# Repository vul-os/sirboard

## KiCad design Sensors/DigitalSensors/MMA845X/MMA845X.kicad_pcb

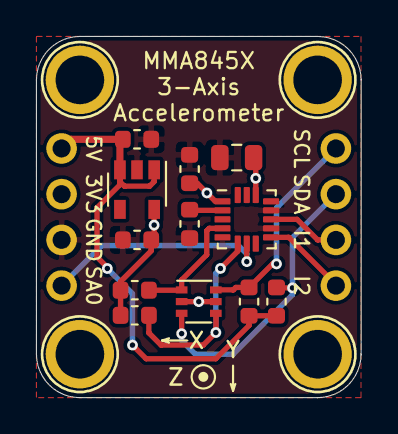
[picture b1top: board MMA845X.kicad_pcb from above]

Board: 2 copper layers, 18.0 x 20.1 mm, 18 parts (0 on the bottom side), 11 nets.

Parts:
C1, C3: 1uF; C_0603_1608Metric
C2, C4: 100nF; C_0603_1608Metric
C5: 4.7uF; C_0805_2012Metric
H1, H2, H3, H4: MountingHole; MountingHole_M2.5_SirBoard
J1, J2: Conn_01x04; PinHeader_1x04_P2.54mm_Vertical
Q1: BSS138DW; SOT-363_SC-70-6
R1, R2, R3, R4: 4K7; R_0603_1608Metric
U1: AP2127K-3.3; SOT-23-5
U2: MMA8451; QFN-COL-16-P=0.5

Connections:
3V3: C2.1, C3.1, C5.1, J1.2, Q1.2, Q1.5, R1.2, R3.2, U1.5, U2.1, U2.14
5V: C1.1, J1.1, R2.1, R4.1, U1.1, U1.3
GND: C1.2, C2.2, C3.2, C4.2, C5.2, J1.3, U1.2, U2.5, U2.10, U2.12
INT1: J2.3, U2.11
INT2: J2.4, U2.9
unnamed: C4.1, U2.2
SA0: J1.4, U2.7
SCL_3V3: Q1.1, R1.1, U2.4
SCL_5V: J2.1, Q1.6, R2.2
SDA_3V3: Q1.4, R3.1, U2.6
SDA_5V: J2.2, Q1.3, R4.2

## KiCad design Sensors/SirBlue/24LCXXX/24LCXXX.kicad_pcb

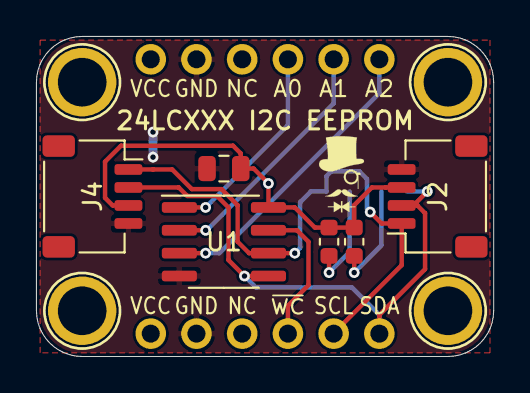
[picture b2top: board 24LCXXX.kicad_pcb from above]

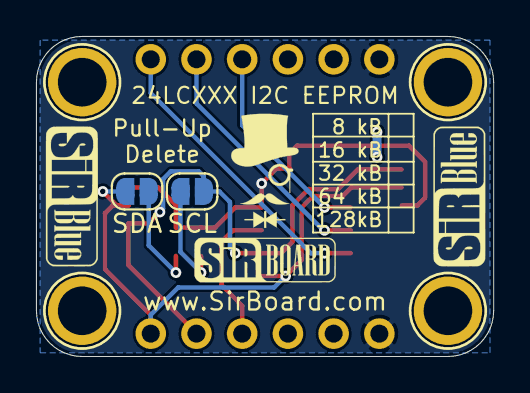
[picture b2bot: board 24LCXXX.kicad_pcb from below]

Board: 2 copper layers, 25.4 x 17.8 mm, 14 parts (4 on the bottom side), 10 nets.

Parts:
C1: 10uF; C_0805_2012Metric
H1, H2, H3, H4: MountingHole; MountingHole_M2.5_SirBoard
J1, J3: Conn_01x06; PinHeader_1x06_P2.54mm_Vertical
J2, J4: Conn_01x04; JST_SH_SM04B-SRSS-TB_1x04-1MP_P1.00mm_Horizontal
R1, R2: 10K; R_0603_1608Metric
SCL: SolderJumper_2_Open; SolderJumper-2_P1.3mm_Open_RoundedPad1.0x1.5mm
SDA: SolderJumper_2_Open; SolderJumper-2_P1.3mm_Open_RoundedPad1.0x1.5mm
U1: 24LC512; SOIC-8_3.9x4.9mm_P1.27mm

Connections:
#WC: J1.4, U1.7
A0: J3.4, U1.1
A1: J3.5, U1.2
A2: J3.6, U1.3
GND: C1.2, J1.2, J2.4, J3.2, J4.4, U1.4
unnamed: R1.2, SDA.2
unnamed: R2.2, SCL.2
SCL: J1.5, J2.1, J4.1, SCL.1, U1.6
SDA: J1.6, J2.2, J4.2, SDA.1, U1.5
VCC: C1.1, J1.1, J2.3, J3.1, J4.3, R1.1, R2.1, U1.8

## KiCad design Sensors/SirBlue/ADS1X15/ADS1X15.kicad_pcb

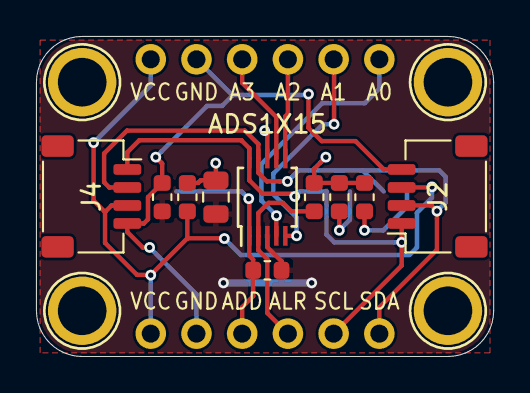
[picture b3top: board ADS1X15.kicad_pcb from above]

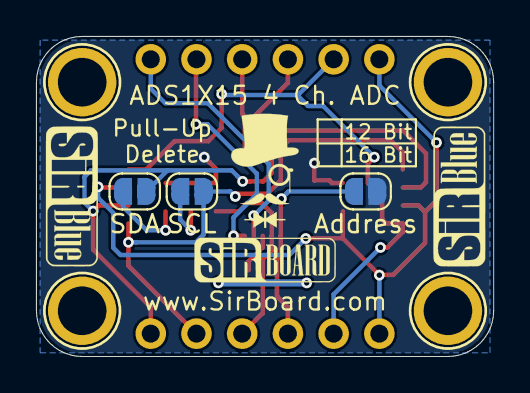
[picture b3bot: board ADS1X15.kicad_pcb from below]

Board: 2 copper layers, 25.4 x 17.8 mm, 19 parts (5 on the bottom side), 14 nets.

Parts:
ADS1X15: ADS1X15; TSSOP-10_3x3mm_P0.5mm
Address: SolderJumper_2_Open; SolderJumper-2_P1.3mm_Open_RoundedPad1.0x1.5mm
C1: 10uF; C_0805_2012Metric
FB1, FB2: Ferrite_Bead; L_0603_1608Metric
H1, H2, H3, H4: MountingHole; MountingHole_M2.5_SirBoard
J1, J3: Conn_01x06; PinHeader_1x06_P2.54mm_Vertical
J2, J4: Conn_01x04; JST_SH_SM04B-SRSS-TB_1x04-1MP_P1.00mm_Horizontal
R1, R2, R3, R4: 10K; R_0603_1608Metric
SCL: SolderJumper_2_Open; SolderJumper-2_P1.3mm_Open_RoundedPad1.0x1.5mm
SDA: SolderJumper_2_Open; SolderJumper-2_P1.3mm_Open_RoundedPad1.0x1.5mm

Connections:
ADDRESS: ADS1X15.1, Address.2, J1.3, R4.1
ALERT: ADS1X15.2, J1.4, R3.2
Ain0: ADS1X15.4, J3.6
Ain1: ADS1X15.5, J3.5
Ain2: ADS1X15.6, J3.4
Ain3: ADS1X15.7, J3.3
GND: FB2.1, J1.2, J2.4, J3.2, J4.4
GND_B: ADS1X15.3, C1.2, FB2.2, R4.2
unnamed: R1.2, SCL.2
unnamed: R2.2, SDA.2
SCL: ADS1X15.10, J1.5, J2.1, J4.1, SCL.1
SDA: ADS1X15.9, J1.6, J2.2, J4.2, SDA.1
VCC: FB1.1, J1.1, J2.3, J3.1, J4.3
VCC_B: ADS1X15.8, Address.1, C1.1, FB1.2, R1.1, R2.1, R3.1

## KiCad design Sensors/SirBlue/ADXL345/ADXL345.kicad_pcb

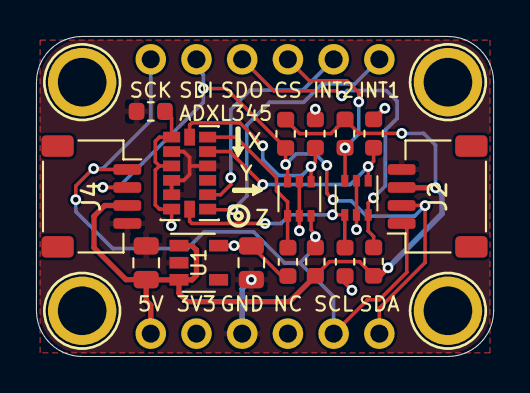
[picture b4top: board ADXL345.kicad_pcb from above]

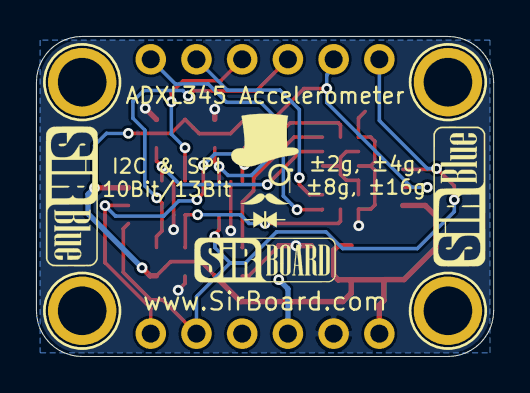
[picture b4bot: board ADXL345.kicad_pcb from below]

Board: 2 copper layers, 25.4 x 17.8 mm, 23 parts (2 on the bottom side), 13 nets.

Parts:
ADXL345: ADXL345; LGA-14_3x5mm_P0.8mm_LayoutBorder1x6y
C1, C4: 10uF; C_0805_2012Metric
C2: 100nF; C_0603_1608Metric
H1, H2, H3, H4: MountingHole; MountingHole_M2.5_SirBoard
J1, J3: Conn_01x06; PinHeader_1x06_P2.54mm_Vertical
J2, J4: Conn_01x04; JST_SH_SM04B-SRSS-TB_1x04-1MP_P1.00mm_Horizontal
Q1, Q2: BSS138DW; SOT-363_SC-70-6
R1, R2, R3, R4, R5, R6, R7, R8: 10K; R_0603_1608Metric
U1: AP2127K-3.3; SOT-23-5

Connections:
3V3: ADXL345.1, ADXL345.3, ADXL345.6, C2.1, C4.1, J1.2, Q1.2, Q1.5, Q2.2, Q2.5, R1.2, R3.2, R5.2, R7.2, U1.5
5V: C1.1, J1.1, J2.3, J4.3, R2.1, R4.1, R6.1, R8.1, U1.1, U1.3
CS_3V3: ADXL345.7, Q1.4, R3.1
CS_5V: J3.4, Q1.3, R4.2
GND: ADXL345.2, ADXL345.4, ADXL345.5, ADXL345.11, C1.2, C2.2, C4.2, J1.3, J2.4, J4.4, U1.2
INT1: ADXL345.8, J3.6
INT2: ADXL345.9, J3.5
SCL_3V3: ADXL345.14, Q2.1, R5.1
SCL_5V: J1.5, J2.1, J3.1, J4.1, Q2.6, R6.2
SDA_3V3: ADXL345.13, Q2.4, R7.1
SDA_5V: J1.6, J2.2, J3.2, J4.2, Q2.3, R8.2
SDO_3V3: ADXL345.12, Q1.1, R1.1
SDO_5V: J3.3, Q1.6, R2.2

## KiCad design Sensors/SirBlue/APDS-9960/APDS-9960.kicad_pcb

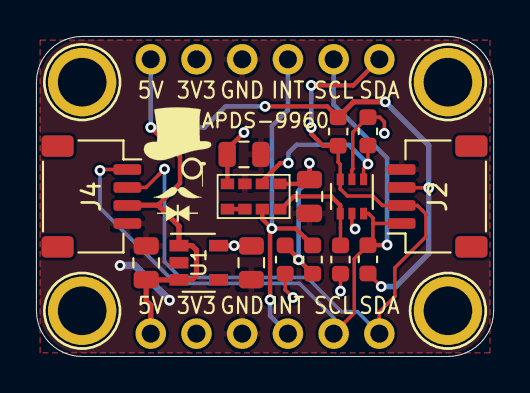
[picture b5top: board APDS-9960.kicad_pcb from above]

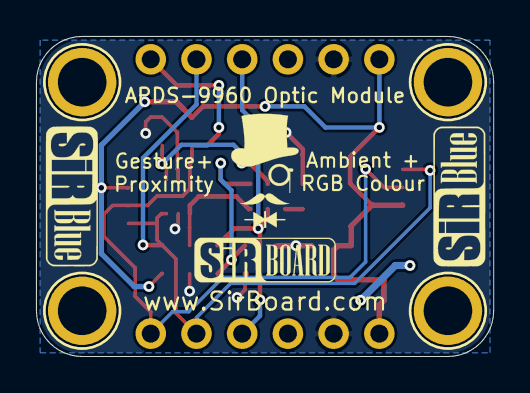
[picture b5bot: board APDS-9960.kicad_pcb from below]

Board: 2 copper layers, 25.4 x 17.8 mm, 21 parts (2 on the bottom side), 10 nets.

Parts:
C1, C4: 10uF; C_0805_2012Metric
C2, C3: 1uF; C_0805_2012Metric
H1, H2, H3, H4: MountingHole; MountingHole_M2.5_SirBoard
J1, J3: Conn_01x06; PinHeader_1x06_P2.54mm_Vertical
J2, J4: Conn_01x04; JST_SH_SM04B-SRSS-TB_1x04-1MP_P1.00mm_Horizontal
Q2: BSS138DW; SOT-363_SC-70-6
R1: 22E; R_0603_1608Metric
R2, R5, R6, R7, R8: 10K; R_0603_1608Metric
U1: AP2127K-3.3; SOT-23-5
U2: APDS-9960; DFN8_2.4mmX4mm_P=0.72

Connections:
3V3: C2.1, C4.1, J1.2, J3.2, Q2.2, Q2.5, R1.1, R5.2, R7.2, U1.5, U2.5
5V: C1.1, J1.1, J2.3, J3.1, J4.3, R6.1, R8.1, U1.1, U1.3
GND: C1.2, C2.2, C3.2, C4.2, J1.3, J2.4, J3.3, J4.4, U1.2, U2.6
INT: J1.4, J3.4, R2.2, U2.2
unnamed: C3.1, R1.2, R2.1, U2.8
unnamed: U2.3, U2.4
SCL_3V3: Q2.1, R5.1, U2.7
SCL_5V: J1.5, J2.1, J3.5, J4.1, Q2.6, R6.2
SDA_3V3: Q2.4, R7.1, U2.1
SDA_5V: J1.6, J2.2, J3.6, J4.2, Q2.3, R8.2

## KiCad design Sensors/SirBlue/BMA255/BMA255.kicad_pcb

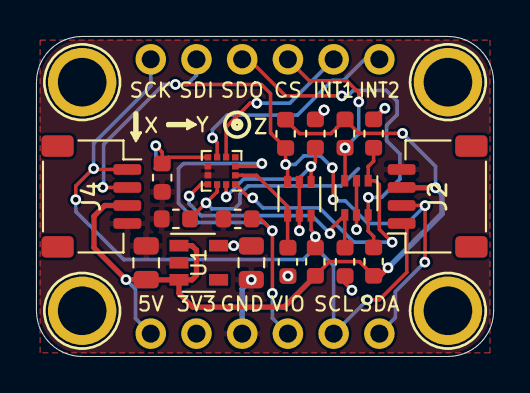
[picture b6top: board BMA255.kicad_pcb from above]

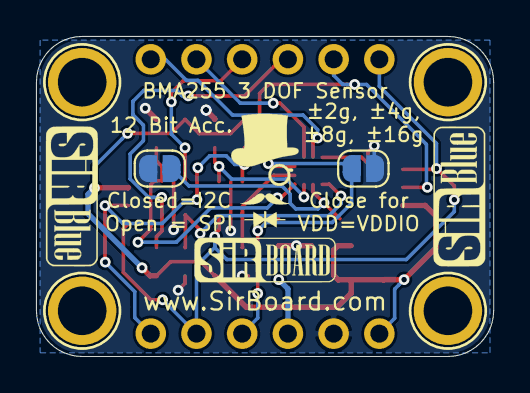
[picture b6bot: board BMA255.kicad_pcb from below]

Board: 2 copper layers, 25.4 x 17.8 mm, 27 parts (4 on the bottom side), 15 nets.

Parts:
C1, C4: 10uF; C_0805_2012Metric
C3: 1uF; C_0603_1608Metric
C5: 100nF; C_0603_1608Metric
H1, H2, H3, H4: MountingHole; MountingHole_M2.5_SirBoard
J1, J3: Conn_01x06; PinHeader_1x06_P2.54mm_Vertical
J2, J4: Conn_01x04; JST_SH_SM04B-SRSS-TB_1x04-1MP_P1.00mm_Horizontal
JP1, JP2: SolderJumper_2_Open; SolderJumper-2_P1.3mm_Open_RoundedPad1.0x1.5mm
Q1, Q2: BSS138DW; SOT-363_SC-70-6
R1, R2, R3, R4, R5, R6, R7, R8, R9: 10K; R_0603_1608Metric
U1: AP2127K-3.3; SOT-23-5
U2: BMA255; LGA-12_2x2mm_P0.5mm

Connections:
3V3: C3.1, C4.1, J1.2, JP1.1, JP2.2, Q1.2, Q1.5, Q2.2, Q2.5, R1.2, R3.2, R5.2, R7.2, U1.5, U2.7
5V: C1.1, J1.1, J2.3, J4.3, R2.1, R4.1, R6.1, R8.1, U1.1, U1.3
CS_3V3: Q1.4, R3.1, U2.10
CS_5V: J3.4, Q1.3, R4.2
GND: C1.2, C3.2, C4.2, C5.2, J1.3, J2.4, J4.4, R9.2, U1.2, U2.8, U2.9
INT1: J3.5, U2.5
INT2: J3.6, U2.6
unnamed: JP2.1, R9.1, U2.11
SCL_3V3: Q2.1, R5.1, U2.12
SCL_5V: J1.5, J2.1, J3.1, J4.1, Q2.6, R6.2
SDA_3V3: Q2.4, R7.1, U2.2
SDA_5V: J1.6, J2.2, J3.2, J4.2, Q2.3, R8.2
SDO_3V3: Q1.1, R1.1, U2.1
SDO_5V: J3.3, Q1.6, R2.2
VDDIO: C5.1, J1.4, JP1.2, U2.3
